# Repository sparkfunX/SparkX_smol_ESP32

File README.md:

# SparkX smôl ESP32

[*SparkX smôl ESP32 (SPX-18619)*](https://www.sparkfun.com/products/18619)

The ESP32 in smôl format:
- ESP32 Processor
- WiFi antenna
- RTC crystal
- WS2812 RGB LED
- WS25Q128 128Mb Flash memory
- USB-C connector
- CP2102N USB-UART interface with RESET and BOOT control

## Repository Contents

- **/examples** - Example code for the Arduino IDE
- **/Documentation** - Datasheets etc.
- **/Hardware** - Eagle design files
- **LICENSE.md** contains the licence information

## Product Versions

- [SPX-18619](https://www.sparkfun.com/products/18619) - Original SparkX Release.

## License Information

This product is _**open source**_!

Please review the LICENSE.md file for license information.

If you have any questions or concerns on licensing, please contact technical support on our [SparkFun forums](https://forum.sparkfun.com/viewforum.php?f=123).

Distributed as-is; no warranty is given.

- Your friends at SparkFun.

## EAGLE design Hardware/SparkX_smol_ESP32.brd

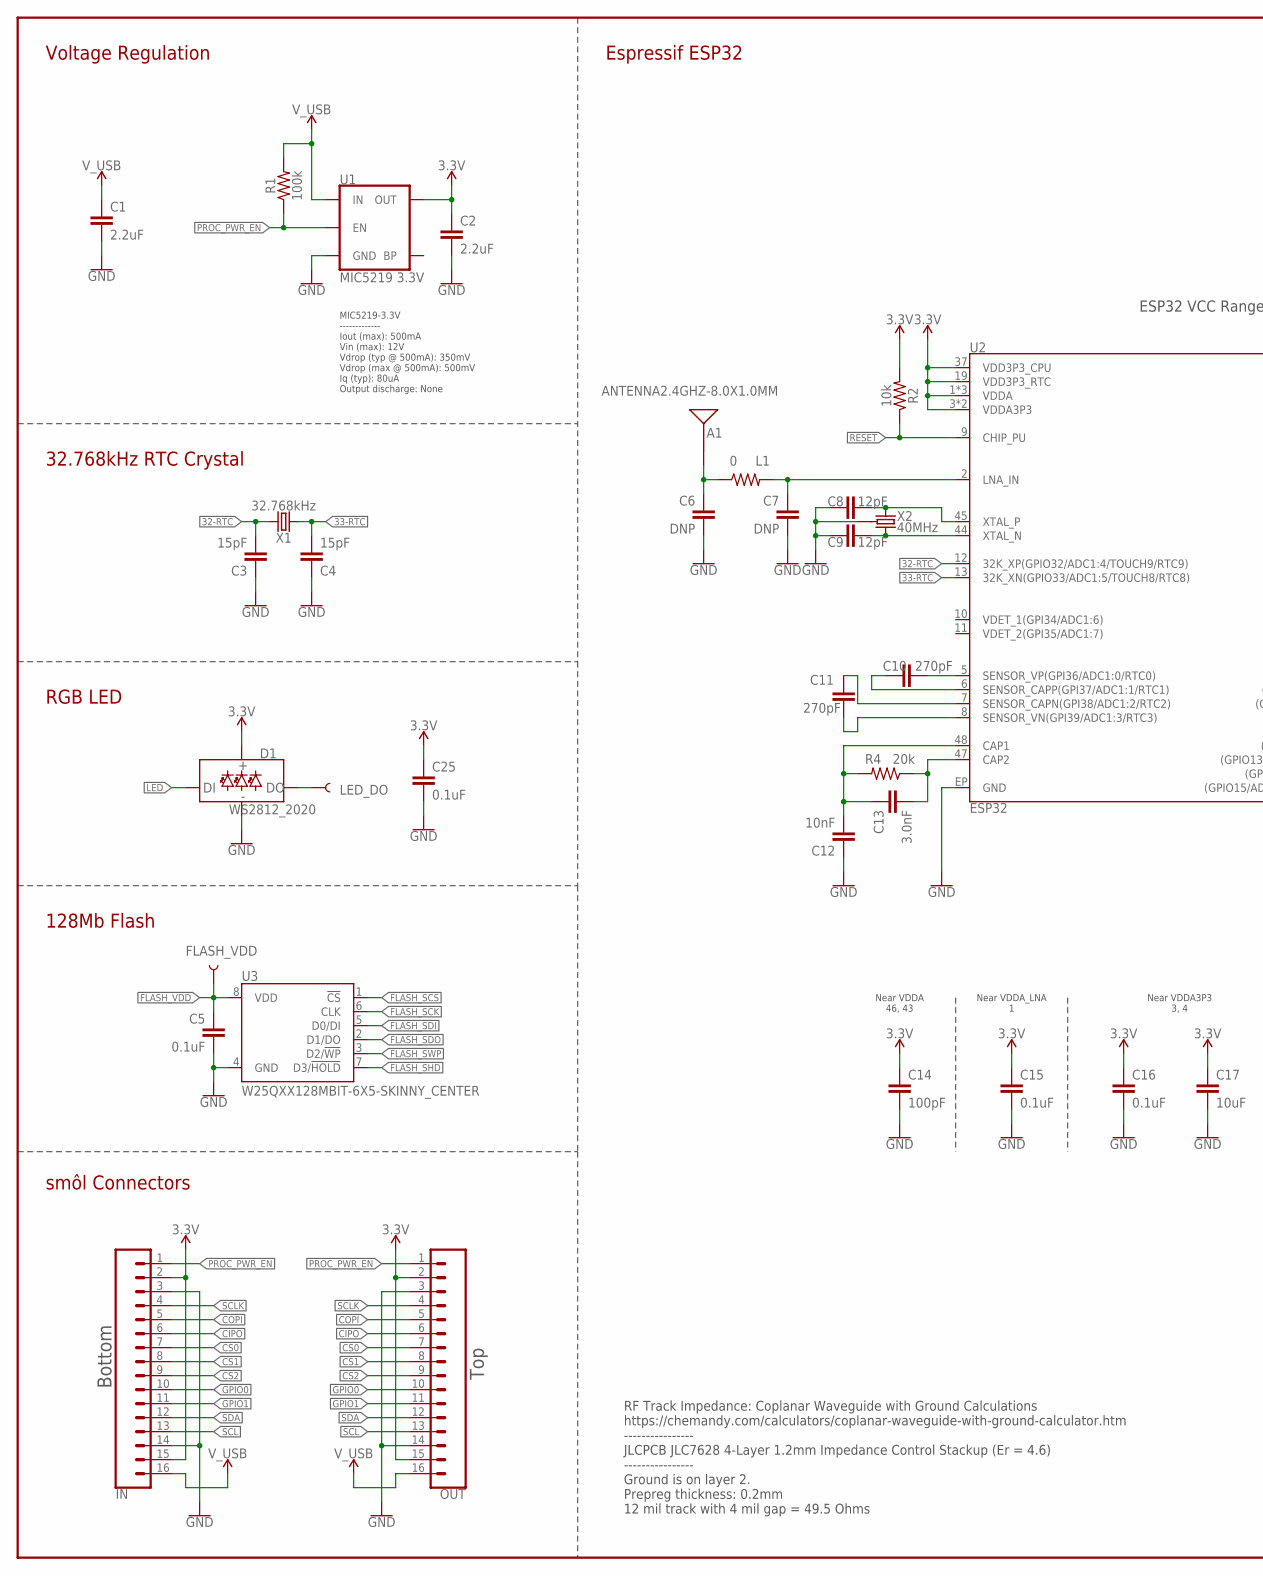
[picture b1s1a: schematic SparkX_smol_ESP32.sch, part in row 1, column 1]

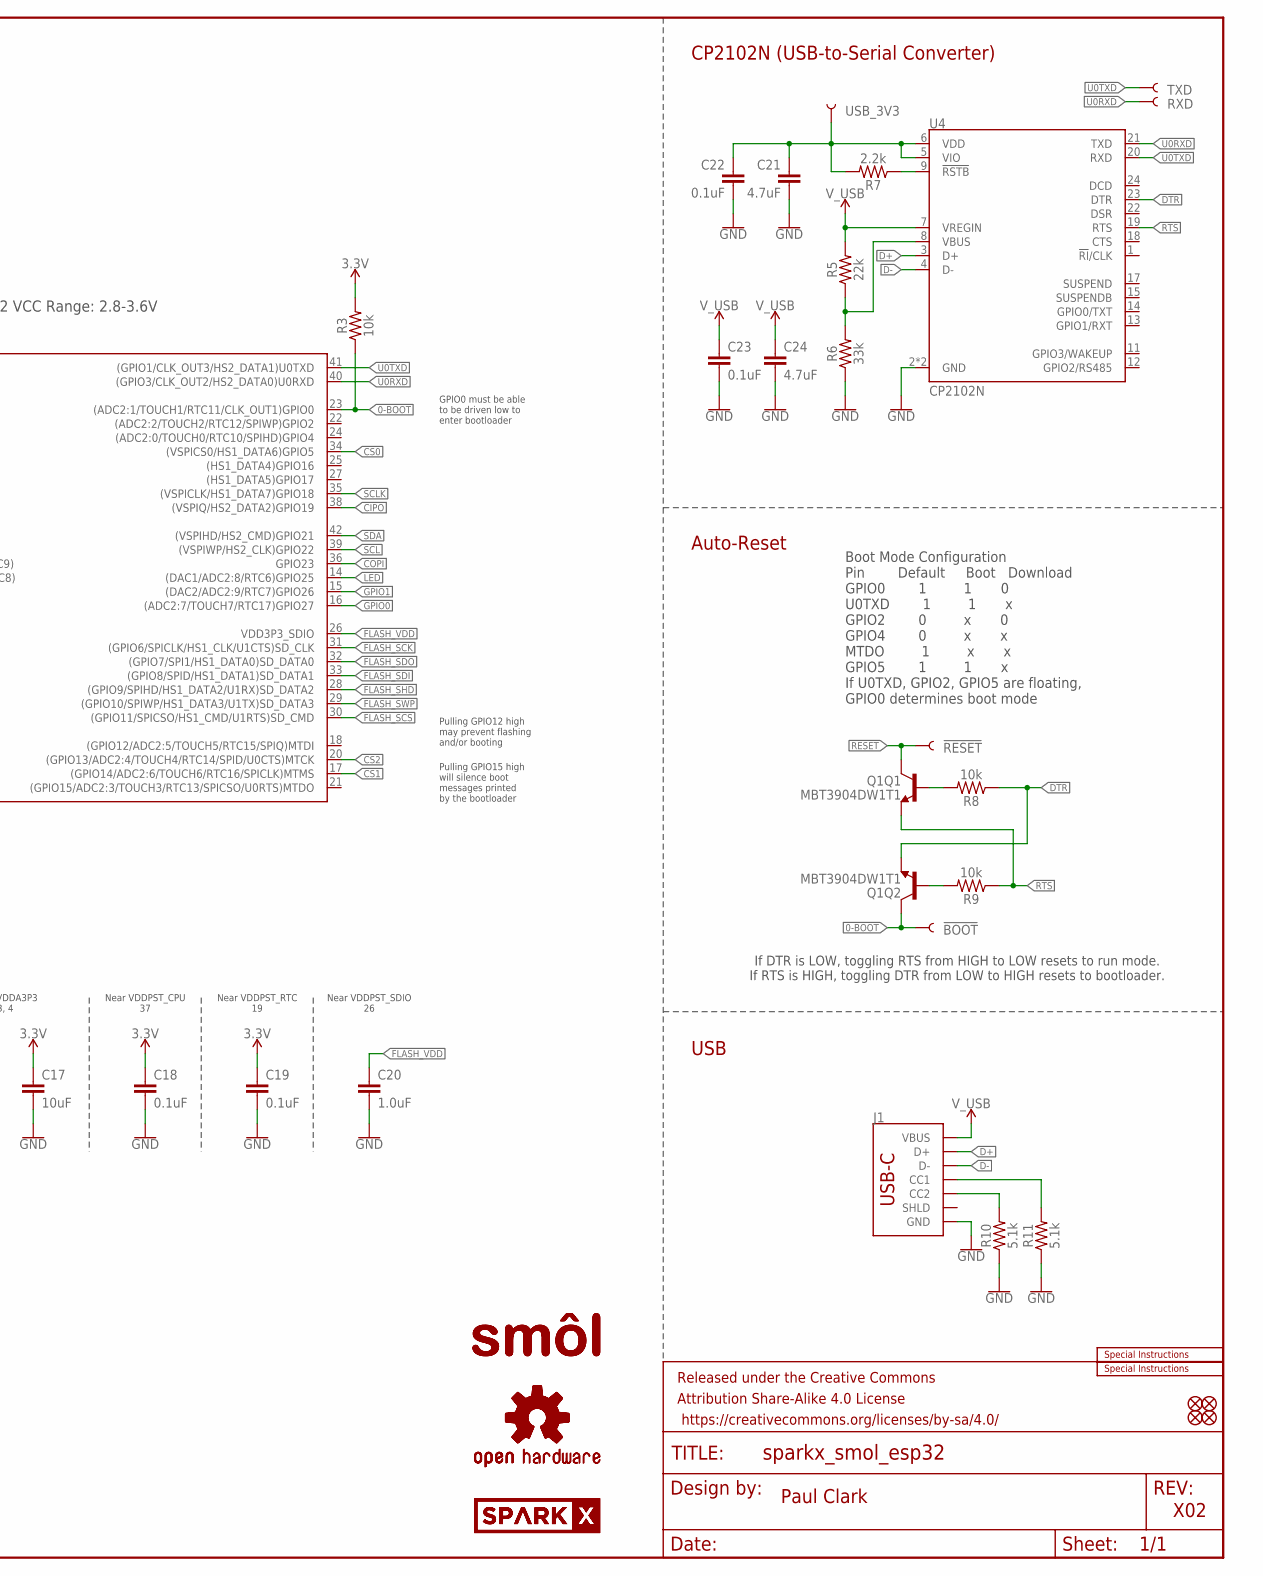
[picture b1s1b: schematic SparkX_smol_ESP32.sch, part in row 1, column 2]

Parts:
!BOOT!: TEST-POINT3X4; PAD.03X.04
!RESET!: TEST-POINT3X4; PAD.03X.04
A1: ANTENNA2.4GHZ-8.0X1.0MM; ANT-2.4GHZ-8.0X1.0MM
C1, C2: 2.2uF; 0402-TIGHT
C3, C4: 15pF; 0402-TIGHT
C5, C15, C16, C18, C19, C22, C23, C25: 0.1uF; 0402-TIGHT
C6, C7: DNP; 0402-TIGHT_NO_CREAM
C8, C9: 12pF; 0402-TIGHT
C10, C11: 270pF; 0402-TIGHT
C12: 10nF; 0402-TIGHT
C13: 3.0nF; 0402-TIGHT
C14: 100pF; 0402-TIGHT
C17: 10uF; 0402-TIGHT
C20: 1.0uF; 0402-TIGHT
C21, C24: 4.7uF; 0402-TIGHT
D1: WS2812_2020; WS2812-2020
FD1, FD2, FD3, FD4: FIDUCIALUFIDUCIAL; FIDUCIAL-MICRO
FLASH_VDD: TEST-POINT3X4; PAD.03X.04
FRAME1: FRAME-LEDGER; CREATIVE_COMMONS
IN: CONN_16FPC_16_0.5MM; FPC_16_0.5MM
J1: USB_C_4-LAYER_PADS; USB-C-16P_4LAYER-PADS
L1: 0; 0402-TIGHT
LED_DO: TEST-POINT3X4; PAD.03X.04
LOGO1: SPECIAL_INSTRUCTIONS-ORDERING; ORDERING_INSTRUCTIONS
LOGO2, LOGO3: OSHW-LOGOMINI; OSHW-LOGO-MINI
LOGO4: SPECIAL_INSTRUCTIONS-PRODUCTION; PRODUCTION_INSTRUCTIONS
OUT: CONN_16FPC_16_0.5MM; FPC_16_0.5MM
Q1: MBT3904DW1T1; SC70-6
R1: 100k; 0402-TIGHT
R2, R3, R8, R9: 10k; 0402-TIGHT
R4: 20k; 0402-TIGHT
R5: 22k; 0402-TIGHT
R6: 33k; 0402-TIGHT
R7: 2.2k; 0402-TIGHT
R10, R11: 5.1k; 0402-TIGHT
RXD: TEST-POINT3X4; PAD.03X.04
TXD: TEST-POINT3X4; PAD.03X.04
U1: MIC5219 3.3V; SOT23-5
U2: ESP32; QFN48-0.4MM
U3: W25QXX128MBIT-6X5-SKINNY_CENTER; WSON-8-6X5-SKINNY_CENTERPAD
U4: CP2102N; QFN24
U$1, U$4: SPARKX-LOGO3; SPARKX-SMALL
U$14, U$15: SMOL_LOGOSMALL; SMOL_SMALL
USB_3V3: TEST-POINT3X4; PAD.03X.04
X1: 32.768kHz; CRYSTAL-SMD-3.2X1.5MM
X2: 40MHz; CRYSTAL-SMD-2X2.5MM

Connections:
0-!BOOT!: !BOOT!.1, Q1.6 (C), R3.1, U2.23 ((ADC2:1/TOUCH1/RTC11/CLK_OUT1)GPIO0)
1: C11.1, U2.7 (SENSOR_CAPN(GPI38/ADC1:2/RTC2))
3: C10.2, U2.5 (SENSOR_VP(GPI36/ADC1:0/RTC0))
3.3V: C2.1, C14.1, C15.1, C16.1, C17.1, C18.1, C19.1, C25.1, D1.VCC, IN.2, IN.15, OUT.2, OUT.15, R2.2, R3.2, U1.5 (OUT), U2.1 (VDDA), U2.3 (VDDA3P3), U2.4 (VDDA3P3), U2.19 (VDD3P3_RTC), U2.37 (VDD3P3_CPU), U2.43 (VDDA), U2.46 (VDDA)
6: C10.1, U2.6 (SENSOR_CAPP(GPI37/ADC1:1/RTC1))
32-RTC: C3.2, U2.12 (32K_XP(GPIO32/ADC1:4/TOUCH9/RTC9)), X1.P$1 (1)
33-RTC: C4.2, U2.13 (32K_XN(GPIO33/ADC1:5/TOUCH8/RTC8)), X1.P$2 (2)
!RESET: !RESET!.1, Q1.3 (C), R2.1, U2.9 (CHIP_PU)
CAP_10N1: C12.2, C13.1, R4.2, U2.48 (CAP1)
CIPO: IN.6, OUT.6, U2.38 ((VSPIQ/HS2_DATA2)GPIO19)
COPI: IN.5, OUT.5, U2.36 (GPIO23)
CS0: IN.7, OUT.7, U2.34 ((VSPICS0/HS1_DATA6)GPIO5)
CS1: IN.8, OUT.8, U2.17 ((GPIO14/ADC2:6/TOUCH6/RTC16/SPICLK)MTMS)
CS2: IN.9, OUT.9, U2.20 ((GPIO13/ADC2:4/TOUCH4/RTC14/SPID/U0CTS)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)
D+: J1.A6 (D+), J1.B6 (D+), U4.3 (D+)
D-: J1.A7 (D-), J1.B7 (D-), U4.4 (D-)
DTR: Q1.1 (E), R8.1, U4.23 (DTR)
FLASH_SCK: U2.31 ((GPIO6/SPICLK/HS1_CLK/U1CTS)SD_CLK), U3.6 (CLK)
FLASH_SCS: U2.30 ((GPIO11/SPICSO/HS1_CMD/U1RTS)SD_CMD), U3.1 (!CS!)
FLASH_SDI: U2.33 ((GPIO8/SPID/HS1_DATA1)SD_DATA1), U3.5 (D0/DI)
FLASH_SDO: U2.32 ((GPIO7/SPI1/HS1_DATA0)SD_DATA0), U3.2 (D1/DO)
FLASH_SHD: U2.28 ((GPIO9/SPIHD/HS1_DATA2/U1RX)SD_DATA2), U3.7 (D3/!HOLD!)
FLASH_SWP: U2.29 ((GPIO10/SPIWP/HS1_DATA3/U1TX)SD_DATA3), U3.3 (D2/!WP!)
FLASH_VDD: C5.1, C20.1, FLASH_VDD.1, U2.26 (VDD3P3_SDIO), U3.8 (VDD)
GND: C1.2, C2.2, C3.1, C4.1, C5.2, C6.2, C7.2, C8.1, C9.1, C12.1, C14.2, C15.2, C16.2, C17.2, C18.2, C19.2, C20.2, C21.2, C22.2, C23.2, C24.2, C25.2, D1.GND, IN.3, IN.14, J1.GND, J1.GND2 (GND), OUT.3, OUT.14, R6.1, R10.1, R11.1, U1.2 (GND), U2.EP (GND), U3.4 (GND), U4.2 (GND), U4.PAD (GND), X2.P2 (GND), X2.P4 (GND)
GPIO0: IN.10, OUT.10, U2.16 ((ADC2:7/TOUCH7/RTC17)GPIO27)
GPIO1: IN.11, OUT.11, U2.15 ((DAC2/ADC2:9/RTC7)GPIO26)
LED: D1.DI, U2.14 ((DAC1/ADC2:8/RTC6)GPIO25)
unnamed: J1.A5 (CC1), R11.2
unnamed: J1.B5 (CC2), R10.2
unnamed: C11.2, U2.8 (SENSOR_VN(GPI39/ADC1:3/RTC3))
unnamed: D1.DO, LED_DO.1
unnamed: Q1.5 (B), R8.2
unnamed: Q1.2 (B), R9.2
unnamed: C8.2, U2.45 (XTAL_P), X2.P1 (1)
unnamed: C9.2, U2.44 (XTAL_N), X2.P3 (2)
unnamed: C13.2, R4.1, U2.47 (CAP2)
unnamed: R5.1, R6.2, U4.8 (VBUS)
unnamed: R7.1, U4.9 (!RSTB)
unnamed: A1.FEED, C6.1, L1.1
unnamed: C7.1, L1.2, U2.2 (LNA_IN)
PROC_PWR_EN: IN.1, OUT.1, R1.1, U1.3 (EN)
RTS: Q1.4 (E), R9.1, U4.19 (RTS)
SCL: IN.13, OUT.13, U2.39 ((VSPIWP/HS2_CLK)GPIO22)
SCLK: IN.4, OUT.4, U2.35 ((VSPICLK/HS1_DATA7)GPIO18)
SDA: IN.12, OUT.12, U2.42 ((VSPIHD/HS2_CMD)GPIO21)
U0RXD: RXD.1, U2.40 ((GPIO3/CLK_OUT2/HS2_DATA0)U0RXD), U4.21 (TXD)
U0TXD: TXD.1, U2.41 ((GPIO1/CLK_OUT3/HS2_DATA1)U0TXD), U4.20 (RXD)
USB_3V3: C21.1, C22.1, R7.2, U4.5 (VIO), U4.6 (VDD), USB_3V3.1
V_USB: C1.1, C23.1, C24.1, IN.16, J1.VBUS1 (VBUS), J1.VBUS2 (VBUS), OUT.16, R1.2, R5.2, U1.1 (IN), U4.7 (VREGIN)

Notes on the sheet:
Paul Clark
X02
RF Track Impedance: Coplanar Waveguide with Ground Calculations https://chemandy.com/calculators/coplanar-waveguide-with-ground-calculator.htm ---------------- JLCPCB JLC7628 4-Layer 1.2mm Impedance Control Stackup (Er = 4.6) ---------------- Ground is on layer 2. Prepreg thickness: 0.2mm 12 mil tr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
smôl Connectors
Bottom
Top
Boot Mode Configuration Pin Default Boot Download GPIO0 1 1 0 U0TXD 1 1 x GPIO2 0 x 0 GPIO4 0 x x MTDO 1 x x GPIO5 1 1 x If U0TXD, GPIO2, GPIO5 are floating, GPIO0 determines boot mode
Auto-Reset
Near VDDA 46, 43
Near VDDA_LNA 1
Near VDDA3P3 3, 4
Near VDDPST_CPU 37
Near VDDPST_SDIO 26
Near VDDPST_RTC 19
Espressif ESP32
128Mb Flash
32.768kHz RTC Crystal
ESP32 VCC Range: 2.8-3.6V
If DTR is LOW, toggling RTS from HIGH to LOW resets to run mode. If RTS is HIGH, toggling DTR from LOW to HIGH resets to bootloader.
CP2102N (USB-to-Serial Converter)
GPIO0 must be able to be driven low to enter bootloader
Pulling GPIO12 high may prevent flashing and/or booting
Pulling GPIO15 high will silence boot messages printed by the bootloader
USB
MIC5219-3.3V ------------- Iout (max): 500mA Vin (max): 12V Vdrop (typ @ 500mA): 350mV Vdrop (max @ 500mA): 500mV Iq (typ): 80uA Output discharge: None
Voltage Regulation
RGB LED

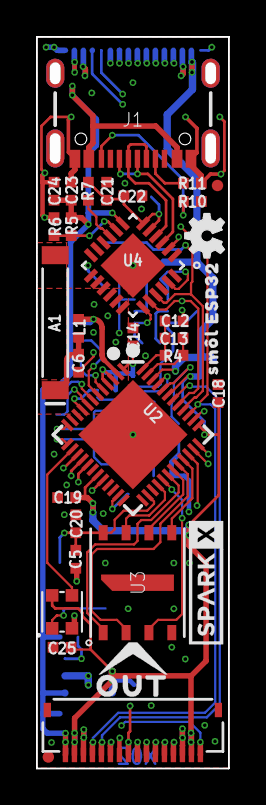
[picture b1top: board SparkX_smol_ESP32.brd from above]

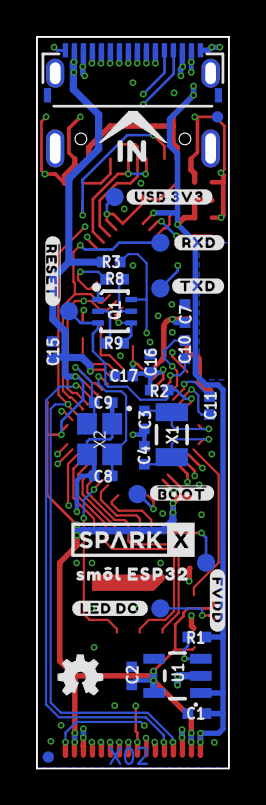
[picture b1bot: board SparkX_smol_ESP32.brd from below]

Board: 4 copper layers, 10.7 x 40.6 mm, 80 parts (43 on the bottom side), 50 nets.

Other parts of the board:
U$5, U$17: SM�L_ESP320
U$6: #TXD#0
U$7: ##BOOT##0
U$8: ##RESET##0
U$9: #USB_3V3#0
U$10: #FVDD#0
U$11: #LED_DO#0
U$12: IN0
U$13: OUT0
U$16: #RXD#0

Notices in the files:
parts and their libraries:
SparkFun-Aesthetics: Licensing: Creative Commons ShareAlike 4.0 International - https://creativecommons.org/licenses/by-sa/4.0
SparkFun-Aesthetics: Released under the Creative Commons Attribution Share-Alike 4.0 License
SparkFun-Aesthetics: https://creativecommons.org/licenses/by-sa/4.0
